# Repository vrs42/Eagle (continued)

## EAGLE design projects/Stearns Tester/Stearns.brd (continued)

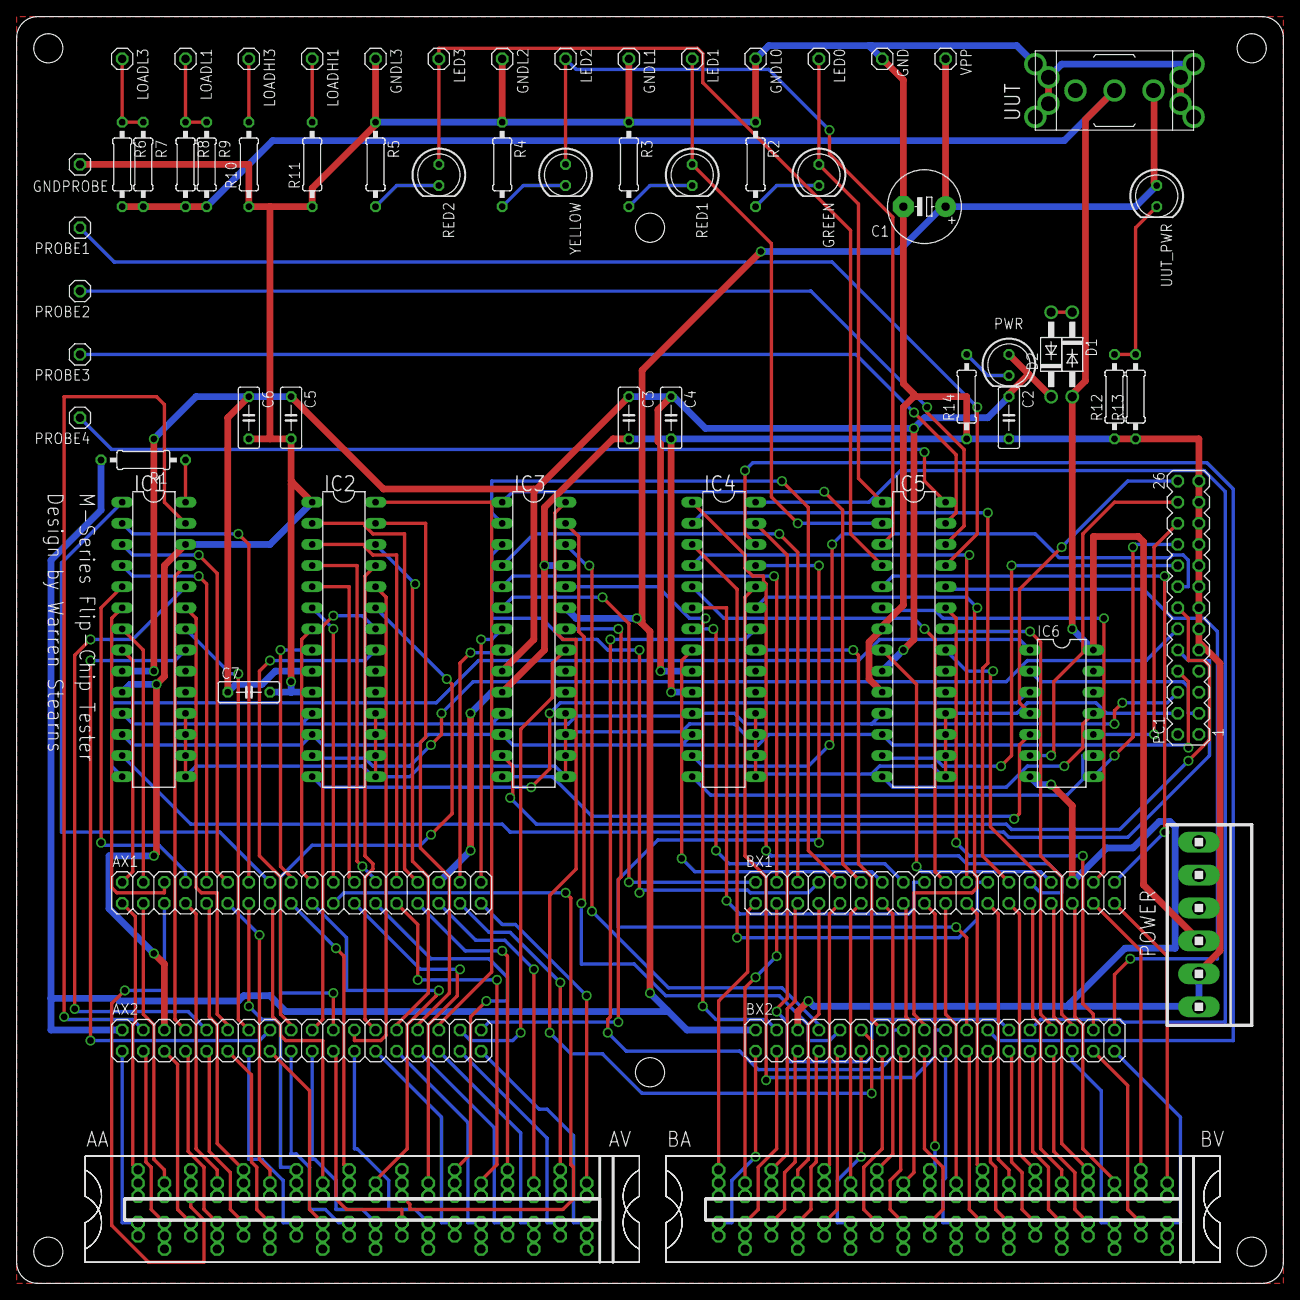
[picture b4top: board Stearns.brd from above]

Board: 2 copper layers, 152.4 x 152.4 mm, 64 parts (0 on the bottom side), 180 nets.
